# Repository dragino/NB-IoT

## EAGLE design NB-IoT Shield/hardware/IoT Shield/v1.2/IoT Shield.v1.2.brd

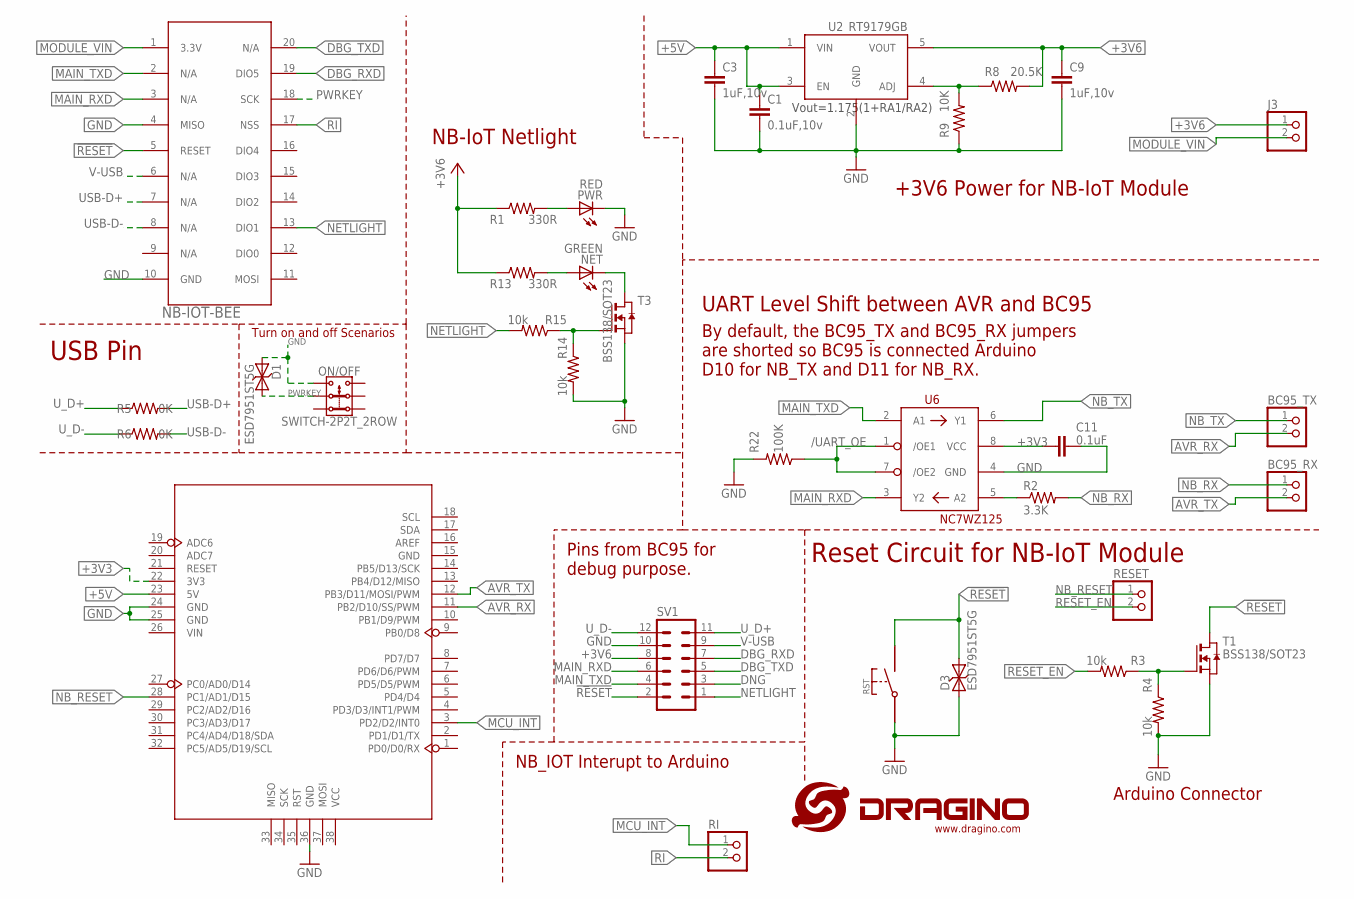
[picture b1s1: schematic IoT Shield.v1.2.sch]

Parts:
BC95_RX, BC95_TX: PINHD-1X2; 1X02
C1: 0.1uF,10v; C0402
C3, C9: 1uF,10v; C0402
C11: 0.1uF; C0402
D1, D3: ESD7951ST5G; SOD−923
IOT-BEE: NB-IOT-BEE; LORA
J3: PINHD-1X2; 1X02
NET: GREEN; CHIP-LED0603
ON/OFF: SWITCH-2P2T_2ROW; KFT7.0-7X7
PWR: RED; CHIP-LED0603
R1, R13: 330R; R0402
R2: 3.3K; R0402
R3, R4, R14, R15: 10k; R0402
R5, R6: 0K; R0402
R8: 20.5K; R0402
R9: 10K; R0402
R22: 100K; R0402
RESET: PINHD-1X2; 1X02
RI: PINHD-1X2; 1X02
RST: SWITCHTS-16; TS-016
SV1: MA06-2
T1, T3: BSS138/SOT23; SOT-23
U2: RT9179GB; SOT23-5
U5: MOUDLE_ARDUINO-38PMOUDLE_ARDUINO-38P_L; MOUDLE_ARDUINO-38P_L
U6: NC7WZ125; US8
U$1: LOGO-NEW; LOGO-SILK-NEW

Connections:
!RESET: D3.P$2 (2), IOT-BEE.5 (RESET), RST.P$2, SV1.2, T1.1 (D)
+3V3: C11.2, U5.22 (3V3), U6.8 (VCC)
+3V6: C9.1, J3.1, R1.1, R8.2, R13.1, SV1.8, U2.5 (VOUT)
+5V: C1.1, C3.1, U2.1 (VIN), U2.3 (EN), U5.23 (5V)
/UART_OE: R22.1, U6.1 (/OE1), U6.7 (/OE2)
AVR_RX: BC95_TX.2, U5.11 (PB2/D10/SS/PWM)
AVR_TX: BC95_RX.2, U5.12 (PB3/D11/MOSI/PWM)
DBG_RXD: IOT-BEE.19 (DIO5), SV1.7
DBG_TXD: IOT-BEE.20 (N/A), SV1.5
DNG: SV1.3
GND: C1.2, C3.2, C9.2, C11.1, D1.P$1 (1), D3.P$1 (1), IOT-BEE.4 (MISO), IOT-BEE.10 (GND), ON/OFF.3.1, PWR.C, R4.2, R9.1, R14.2, R22.2, RST.P$1, SV1.10, T1.2 (S), T3.2 (S), U2.2 (GND), U5.24 (GND), U5.25 (GND), U5.36 (GND), U6.4 (GND)
MAIN_RXD: IOT-BEE.3 (N/A), SV1.6, U6.3 (Y2)
MAIN_TXD: IOT-BEE.2 (N/A), SV1.4, U6.2 (A1)
MCU_INT: RI.1, U5.3 (PD2/D2/INT0)
MODULE_VIN: IOT-BEE.1 (3.3V), J3.2
unnamed: R3.1, R4.1, T1.3 (G)
unnamed: PWR.A, R1.2
unnamed: NET.A, R13.2
unnamed: NET.C, T3.1 (D)
unnamed: R14.1, R15.1, T3.3 (G)
unnamed: R8.1, R9.2, U2.4 (ADJ)
unnamed: R2.1, U6.5 (A2)
NB_RESET: RESET.1, U5.28 (PC1/AD1/D15)
NB_RX: BC95_RX.1, R2.2
NB_TX: BC95_TX.1, U6.6 (Y1)
NETLIGHT: IOT-BEE.13 (DIO1), R15.2, SV1.1
PWRKEY: D1.P$2 (2), IOT-BEE.18 (SCK), ON/OFF.2.1
RESET_EN: R3.2, RESET.2
RI: IOT-BEE.17 (NSS), RI.2
USB-D+: IOT-BEE.7 (N/A), R5.2
USB-D-: IOT-BEE.8 (N/A), R6.2
U_D+: R5.1, SV1.11
U_D-: R6.1, SV1.12
V-USB: IOT-BEE.6 (N/A), SV1.9

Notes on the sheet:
Arduino Connector
By default, the BC95_TX and BC95_RX jumpers are shorted so BC95 is connected Arduino D10 for NB_TX and D11 for NB_RX.
Reset Circuit for NB-IoT Module
UART Level Shift between AVR and BC95
NB_IOT Interupt to Arduino
+3V6 Power for NB-IoT Module
Pins from BC95 for debug purpose.
NB-IoT Netlight
USB Pin
Turn on and off Scenarios

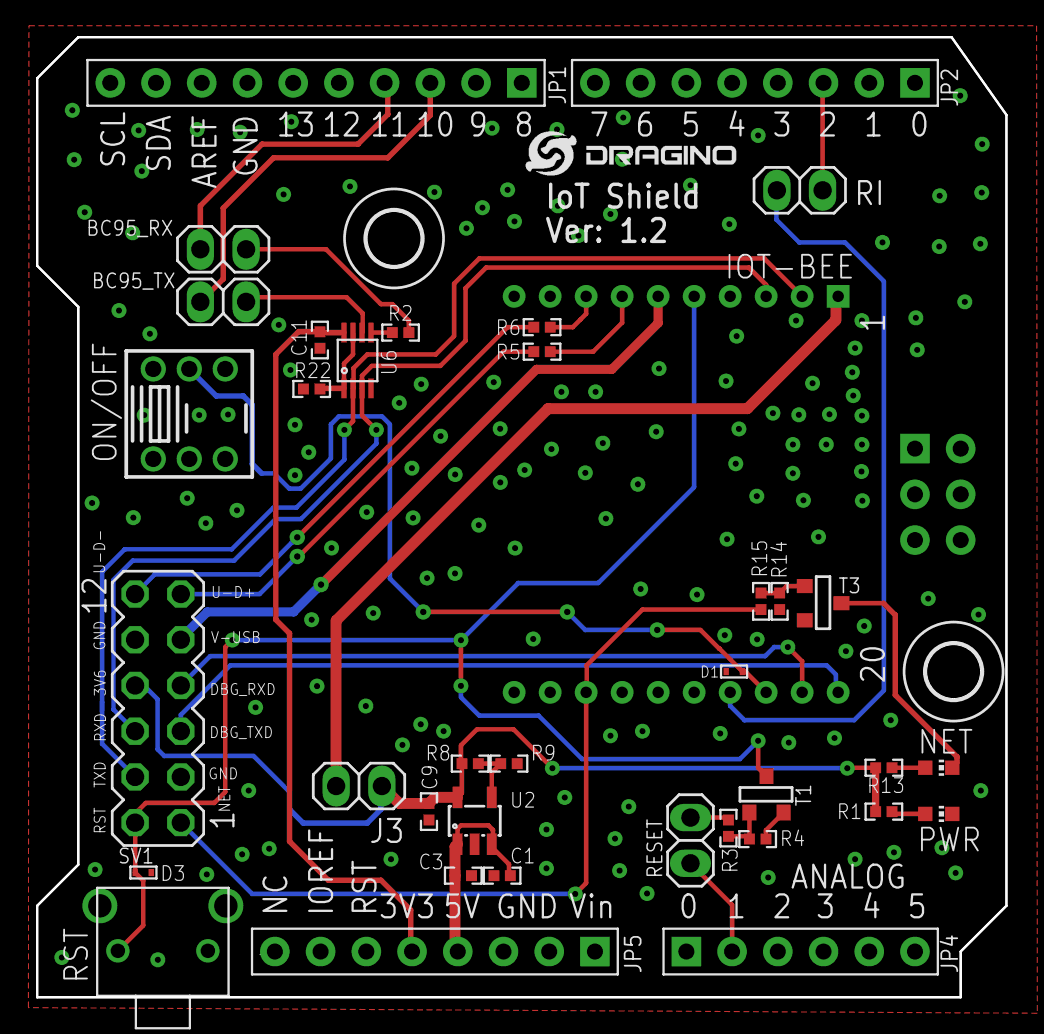
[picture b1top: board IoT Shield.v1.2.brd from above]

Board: 2 copper layers, 53.8 x 53.3 mm, 37 parts (0 on the bottom side), 33 nets.

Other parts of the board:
U$2, U$3: 3,0

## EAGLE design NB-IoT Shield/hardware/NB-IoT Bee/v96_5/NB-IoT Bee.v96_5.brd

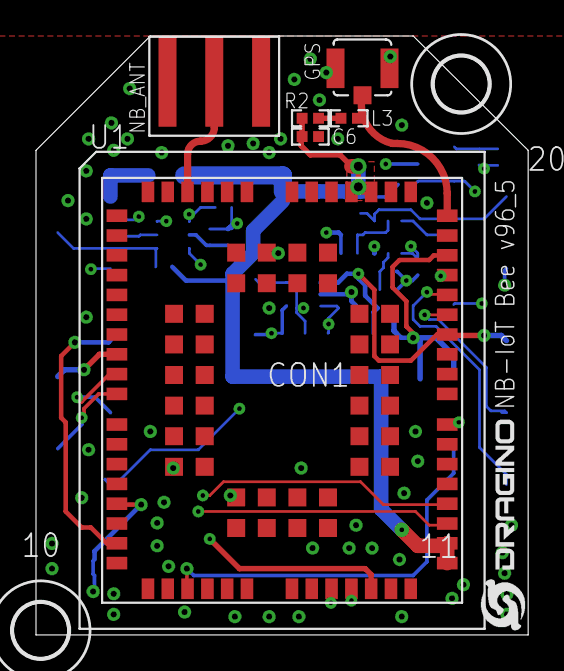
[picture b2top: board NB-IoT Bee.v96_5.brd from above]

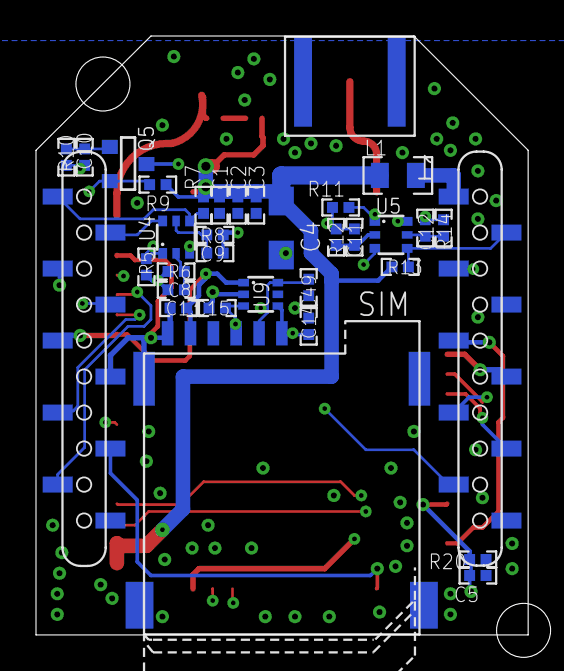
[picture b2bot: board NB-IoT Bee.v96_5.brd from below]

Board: 4 copper layers, 27.3 x 33.3 mm, 41 parts (31 on the bottom side), 33 nets.

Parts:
C1: 22pF; C0402
C2: 100pF; C0402
C3: 0.1uF; C0402
C4: 100uF, 6.3v,钽电容; SMC_A
C5: 0.01u; C0402
C6, C13: 0.1u; C0402
C8, C9, C10, C11, C12: 1nf; C0402
C14, C15, C49: 33pF; C0402
CON1: BEE-SOCKET
GPS: I-PEX
L1: PZ2012D301-1R5TF; C0805
L3: 47nH; C0402
NB_ANT: NL; SMA-KE
Q5: BSS138-7-F; SOT-23
R2: 10R; R0402
R5, R11, R20: 10k; R0402
R6, R8, R10, R12, R14: 4.7k; R0402
R7, R9, R13: 10K; R0402
SIM: SIM_CARD_CON_6MICRO; SIM-MICRO-PUSH
U1: BG96
U4, U5: 2N7002KDW; SOT363-NXP
U9: SMF05C; SOT363
U$1: LOGO-NEW; LOGO-SILK-NEW
U$2, U$3: 3,0

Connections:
!RESET: CON1.5, U1.17
GND: C1.2, C2.2, C3.2, C4.-, C5.1, C6.2, C14.2, C15.2, C49.2, CON1.4, CON1.10, CON1.11, GPS.GND, GPS.GND1, NB_ANT.P$1, NB_ANT.P$2, NB_ANT.P$3, NB_ANT.P$4, R20.2, U1.3, U1.48, U1.50, U1.54, U1.55, U1.58, U1.59, U1.61, U1.62, U1.67, U1.68, U1.69, U1.70, U1.71, U1.72, U1.73, U1.74, U1.79, U1.80, U1.81, U1.82, U1.89, U1.90, U1.91, U1.100, U1.101, U1.102, U9.2
GPS_RXD: CON1.19, U4.6
GPS_TXD: CON1.20, R7.2, U4.4
MAIN_RXD: CON1.3, U5.6
MAIN_TXD: CON1.2, R13.2, U5.4
unnamed: C8.2, R6.2, U4.2
unnamed: L3.1, R2.1
unnamed: C9.2, R8.2, U4.5
unnamed: C10.2, Q5.3, R10.2
unnamed: C12.2, R14.2, U5.5
unnamed: C11.2, R12.2, U5.2
unnamed: GPS.SIG, L3.2, U1.49
NETLIGHT: CON1.13, U1.21
PWRKEY: C5.2, CON1.18, R20.1, U1.15
RF_ANT: NB_ANT.P$5, U1.60
RI: CON1.17, Q5.2, R9.2
RI1: Q5.1, U1.39
UART1_RXD: R11.2, U1.34, U5.1
UART1_TXD: U1.35, U5.3
UART3_RXD: R5.2, U1.28, U4.1
UART3_TXD: U1.27, U4.3
USB_N: CON1.8, U1.10
USB_P: CON1.7, U1.9
USB_VBUS: CON1.6, U1.8
USIM_CLK: C14.1, CON1.9, SIM.CLK, U1.46, U9.4
USIM_DATA: C49.1, CON1.12, SIM.IO, U1.45, U9.6
USIM_GND: C13.2, CON1.15, SIM.GND, SIM.P$1, SIM.P$2, SIM.P$3, SIM.P$4, U1.47
USIM_RST: C15.1, CON1.14, SIM.RST, U1.44, U9.3
USIM_VDD: C13.1, CON1.16, SIM.VCC, U1.43, U9.1
VBAT: C1.1, C2.1, C3.1, C4.+, C6.1, L1.1, R2.2, R7.1, R9.1, R13.1, U1.32, U1.33, U1.52, U1.53
VDD_18: C8.1, C9.1, C10.1, C11.1, C12.1, R5.1, R6.1, R8.1, R10.1, R11.1, R12.1, R14.1, U1.29
VIN: CON1.1, L1.2

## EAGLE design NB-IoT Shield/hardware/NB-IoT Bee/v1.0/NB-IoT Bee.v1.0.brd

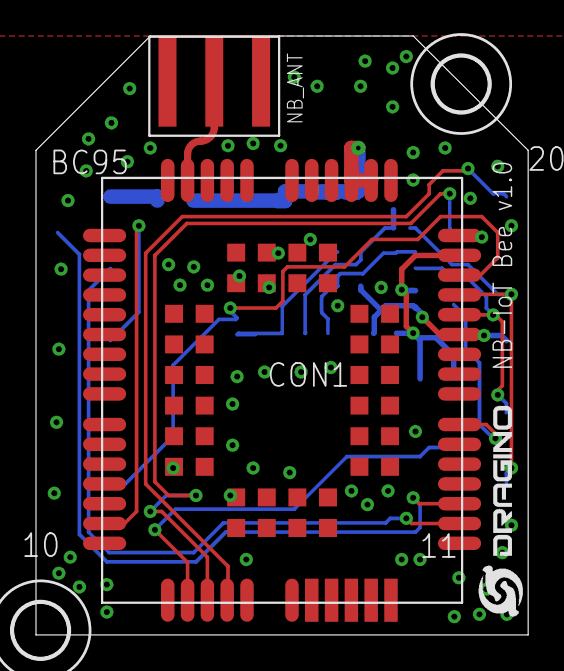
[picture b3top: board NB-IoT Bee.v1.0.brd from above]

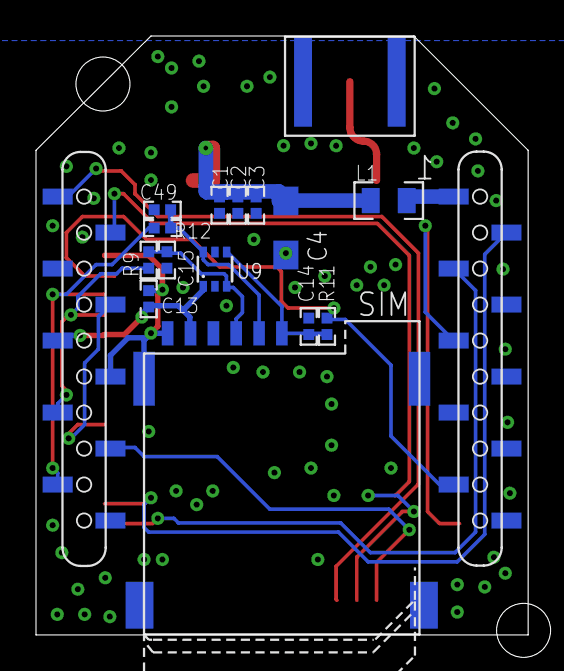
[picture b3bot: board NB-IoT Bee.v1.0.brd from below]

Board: 2 copper layers, 27.3 x 33.3 mm, 20 parts (14 on the bottom side), 19 nets.

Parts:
BC95: BC90
C1: 22pF; C0402
C2: 100pF; C0402
C3: 0.1uF; C0402
C4: 100uF, 6.3v,钽电容; SMC_A
C13: 0.1u; C0402
C14, C15, C49: 33pF; C0402
CON1: BEE-SOCKET
L1: PZ2012D301-1R5TF; C0805
NB_ANT: NL; SMA-KE
R9, R11, R12: 22R; R0402
SIM: SIM_CARD_CON_6MICRO; SIM-MICRO-PUSH
U9: SMF05C; SOT363
U$1: LOGO-NEW; LOGO-SILK-NEW
U$2, U$3: 3,0

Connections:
!RESET: BC95.15, CON1.5
DBG_RXD: BC95.19, CON1.19
DBG_TXD: BC95.20, CON1.20
GND: BC95.2, BC95.43, BC95.47, BC95.48, BC95.51, BC95.52, BC95.54, BC95.59, BC95.60, BC95.61, BC95.62, BC95.63, BC95.64, BC95.65, BC95.66, BC95.71, BC95.72, BC95.73, BC95.74, BC95.81, BC95.82, BC95.83, BC95.92, BC95.93, BC95.94, C1.2, C2.2, C3.2, C4.-, C14.2, C15.2, C49.2, CON1.4, CON1.10, CON1.11, NB_ANT.P$1, NB_ANT.P$2, NB_ANT.P$3, NB_ANT.P$4, U9.2
MAIN_RXD: BC95.29, CON1.3
MAIN_TXD: BC95.30, CON1.2
NETLIGHT: BC95.18, CON1.13
RF_ANT: BC95.53, NB_ANT.P$5
RI: BC95.34, CON1.17
SIM_CLK1: C14.1, R11.1, SIM.CLK, U9.4
SIM_DATA1: C49.1, R12.1, SIM.IO, U9.6
SIM_RST1: C15.1, R9.1, SIM.RST, U9.3
USIM_CLK: BC95.41, CON1.9, R11.2
USIM_DATA: BC95.40, CON1.12, R12.2
USIM_GND: BC95.42, C13.2, CON1.15, SIM.GND, SIM.P$1, SIM.P$2, SIM.P$3, SIM.P$4
USIM_RST: BC95.39, CON1.14, R9.2
USIM_VDD: BC95.38, C13.1, CON1.16, SIM.VCC, U9.1
VIN: CON1.1, L1.2
VIN1: BC95.45, BC95.46, C1.1, C2.1, C3.1, C4.+, L1.1

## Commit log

2018-04-11 Add Readme
2018-04-17 Update NB-IoT Shield hardware source
2018-04-20 nbiot_testing
2018-04-20 DHT711
2018-04-20 NB-IOT
2018-05-11 UDP
    UDP
2018-06-19 update Coap example
    NB-IoT coap program
2018-06-19 updata BC95 UDP
2018-07-10 my_udp
    updata udp
2018-07-10 Add NB-IoT-Bee QB86
2018-07-25 BG96_UDP_TCP
    BG96_UDP_TCP
2018-07-25 Revert "BG96_UDP_TCP"
    This reverts commit bf5500cad2c5f016cca56af5f856ce68123db8fa.
2019-05-09 Update QG96 v96_4 version
2019-08-23 Add Cayenne Examples.
2020-01-30 Update Bee-bg96_v5
2020-03-26 Add NB ST - BC95 ver hardware
2024-02-05 Add NB ST BC660K-GL

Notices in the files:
parts and their libraries:
dragino: http://creativecommons.org/licenses/by-sa/3.0
dragino: Released under the CC Attribution Share-Alike 3.0 License
